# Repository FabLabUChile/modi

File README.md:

modi
====

cheap and fast building robot for swarm behavior research

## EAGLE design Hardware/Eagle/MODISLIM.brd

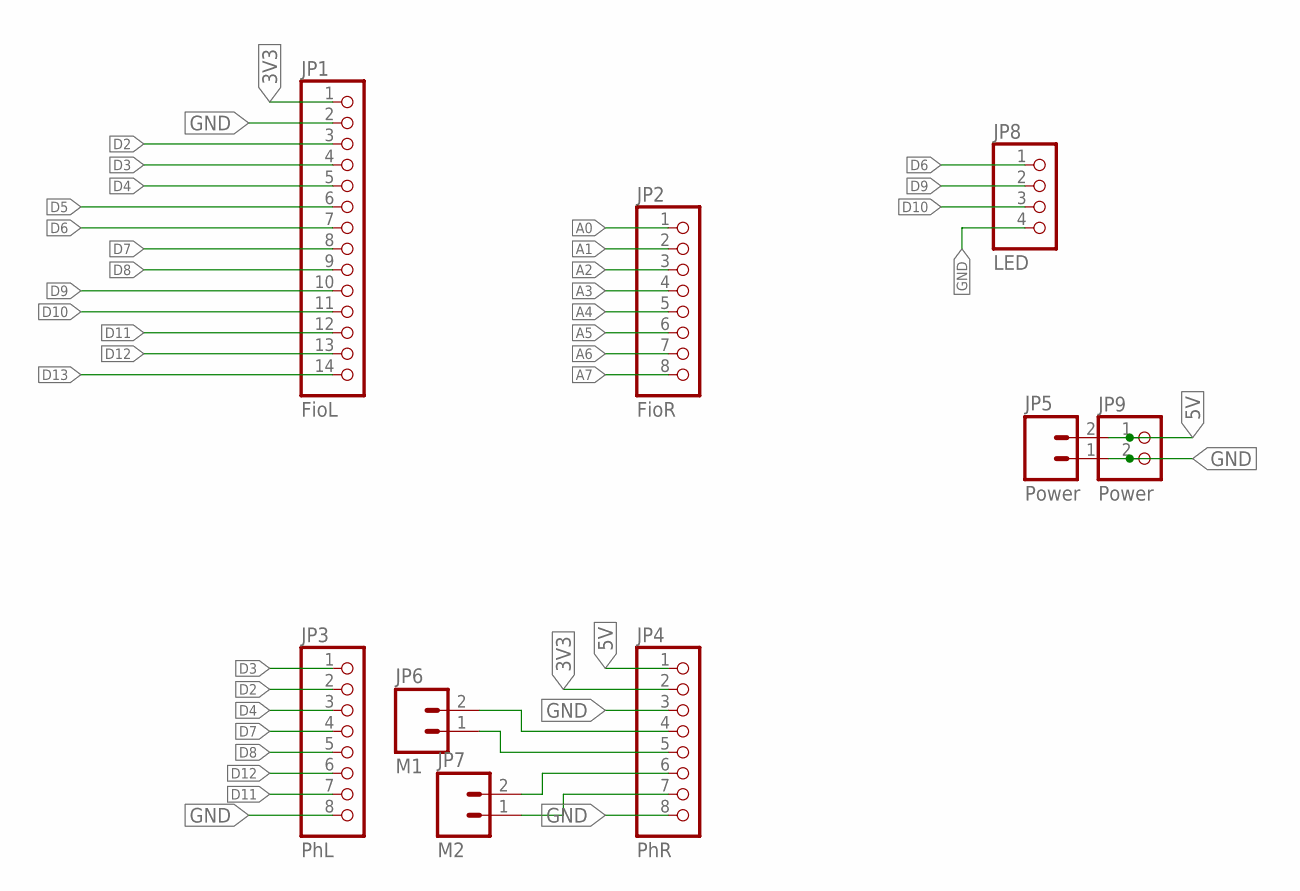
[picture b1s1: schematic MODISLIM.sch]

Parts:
JP1: FioL; 1X14
JP2: FioR; 1X08
JP3: PhL; 1X08
JP4: PhR; 1X08
JP5: Power; SCREWTERMINAL-3.5MM-2
JP6: M1; SCREWTERMINAL-3.5MM-2
JP7: M2; SCREWTERMINAL-3.5MM-2
JP8: LED; 1X04
JP9: Power; 1X02

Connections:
3V3: JP1.1, JP4.2
5V: JP4.1, JP5.2, JP9.1
A0: JP2.1
A1: JP2.2
A2: JP2.3
A3: JP2.4
A4: JP2.5
A5: JP2.6
A6: JP2.7
A7: JP2.8
D2: JP1.3, JP3.2
D3: JP1.4, JP3.1
D4: JP1.5, JP3.3
D5: JP1.6
D6: JP1.7, JP8.1
D7: JP1.8, JP3.4
D8: JP1.9, JP3.5
D9: JP1.10, JP8.2
D10: JP1.11, JP8.3
D11: JP1.12, JP3.7
D12: JP1.13, JP3.6
D13: JP1.14
GND: JP1.2, JP3.8, JP4.3, JP4.8, JP5.1, JP8.4, JP9.2
unnamed: JP4.7, JP7.1
unnamed: JP4.6, JP7.2
unnamed: JP4.5, JP6.1
unnamed: JP4.4, JP6.2

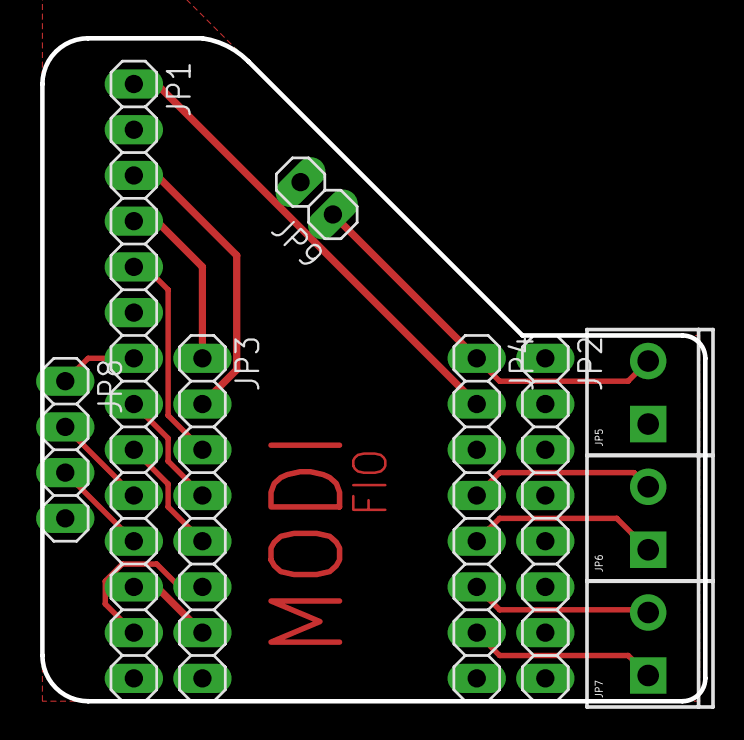
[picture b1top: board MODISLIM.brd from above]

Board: 2 copper layers, 36.8 x 36.8 mm, 9 parts (0 on the bottom side), 17 nets.

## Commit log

2012-11-13 Fernando commiting test
2012-11-20 Main project files added
2012-12-31 testing GitHub Windows
    Valparaíso
2012-12-31 MODIBoard OK
    Update for add XBee support and MODIBoard rev1
2012-12-31 MODI control with Processing
    By testing the best Frame Rate it's 10
2012-12-31 trying to add x axis move
    not lucky yet
2013-01-02 New software -> new bodie
2013-01-02 Revert "New software -> new bodie"
    This reverts commit d780a5ee8f13433e90e3e0d8301f1e04f5b20d63.
2013-01-02 Revert "Revert "New software -> new bodie""
    This reverts commit 5717da78f8244d48f9b85d9ddb98ecb9a29f9ebb.
2013-01-02 tope doble fix
2013-01-03 Chasis mas solido
2013-01-03 Some Pictures
2013-01-04 Ready for print
2013-01-04 topes mas altos
2013-01-05 New body -> new shoes
    New design with new wheels
2013-01-06 README de la seccion Software
    Describe lo que hay en la carpeta para que el uso sea mas guiado.
2013-01-07 fix wheels
2013-01-09 Fix Topes and wheels
    ...and add STL Files
2013-01-09 Update STL
2013-01-09 more filled
2013-04-12 small
2013-04-12 Add some Sweep
2013-04-15 fix topes lipo rider pro
2013-04-19 fix some dimension
2013-04-24 new wheels
2013-05-02 New Look
2013-05-15 expansion board
    Add the expansion feature of chasis
2013-05-17 Thesis
    Latex code for my thesis
2013-05-22 swap motor direction
2013-05-27 Thesis
2013-05-28 renders y thesis
2013-06-03 todo listo para migrar
2013-06-03 test cambio git
2013-06-12 TuioGetAngle
    first version tracking
2013-06-12 MODI meet python
2013-06-13 add gui
    knob in processing for angle controlling
2013-06-13 get angle between MODI & center
2013-07-02 Super intro thesis
2013-07-04 Thesis fun
2013-07-04 ajustes
2013-07-09 cleaning
2013-07-09 chasis ok
2013-07-11 thesis almost ready
2013-07-29 thesis
    Before big changes in chapter 3
2013-08-27 Thesis
    FIN??
